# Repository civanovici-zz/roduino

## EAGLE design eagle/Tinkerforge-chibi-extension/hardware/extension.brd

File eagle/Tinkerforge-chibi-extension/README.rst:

Chibi Extension
===============

This repository contains the hardware design files. 
The software is included in the Master Brick software
and can be found at https://github.com/Tinkerforge/master-brick

Repository Content
------------------

hardware/:
 * Contains kicad project files and additionally schemetics as pdf

datasheets/:
 * Contains datasheets for sensors and complex ICs that are used

Hardware
--------

The hardware is designed with the open source EDA Suite KiCad
(http://kicad.sourceforge.net). Before you are able to open the files,
you have to install the Tinkerforge kicad-libraries
(https://github.com/Tinkerforge/kicad-libraries). You can either clone
them directly in hardware/ or clone them in a seperate folder and
symlink them into hardware/
(ln -s kicad_path/kicad-libraries project_path/hardware). After that you 
can open the .pro file in hardware/ with kicad and from there view and 
modify the schematics and the pcb layout.

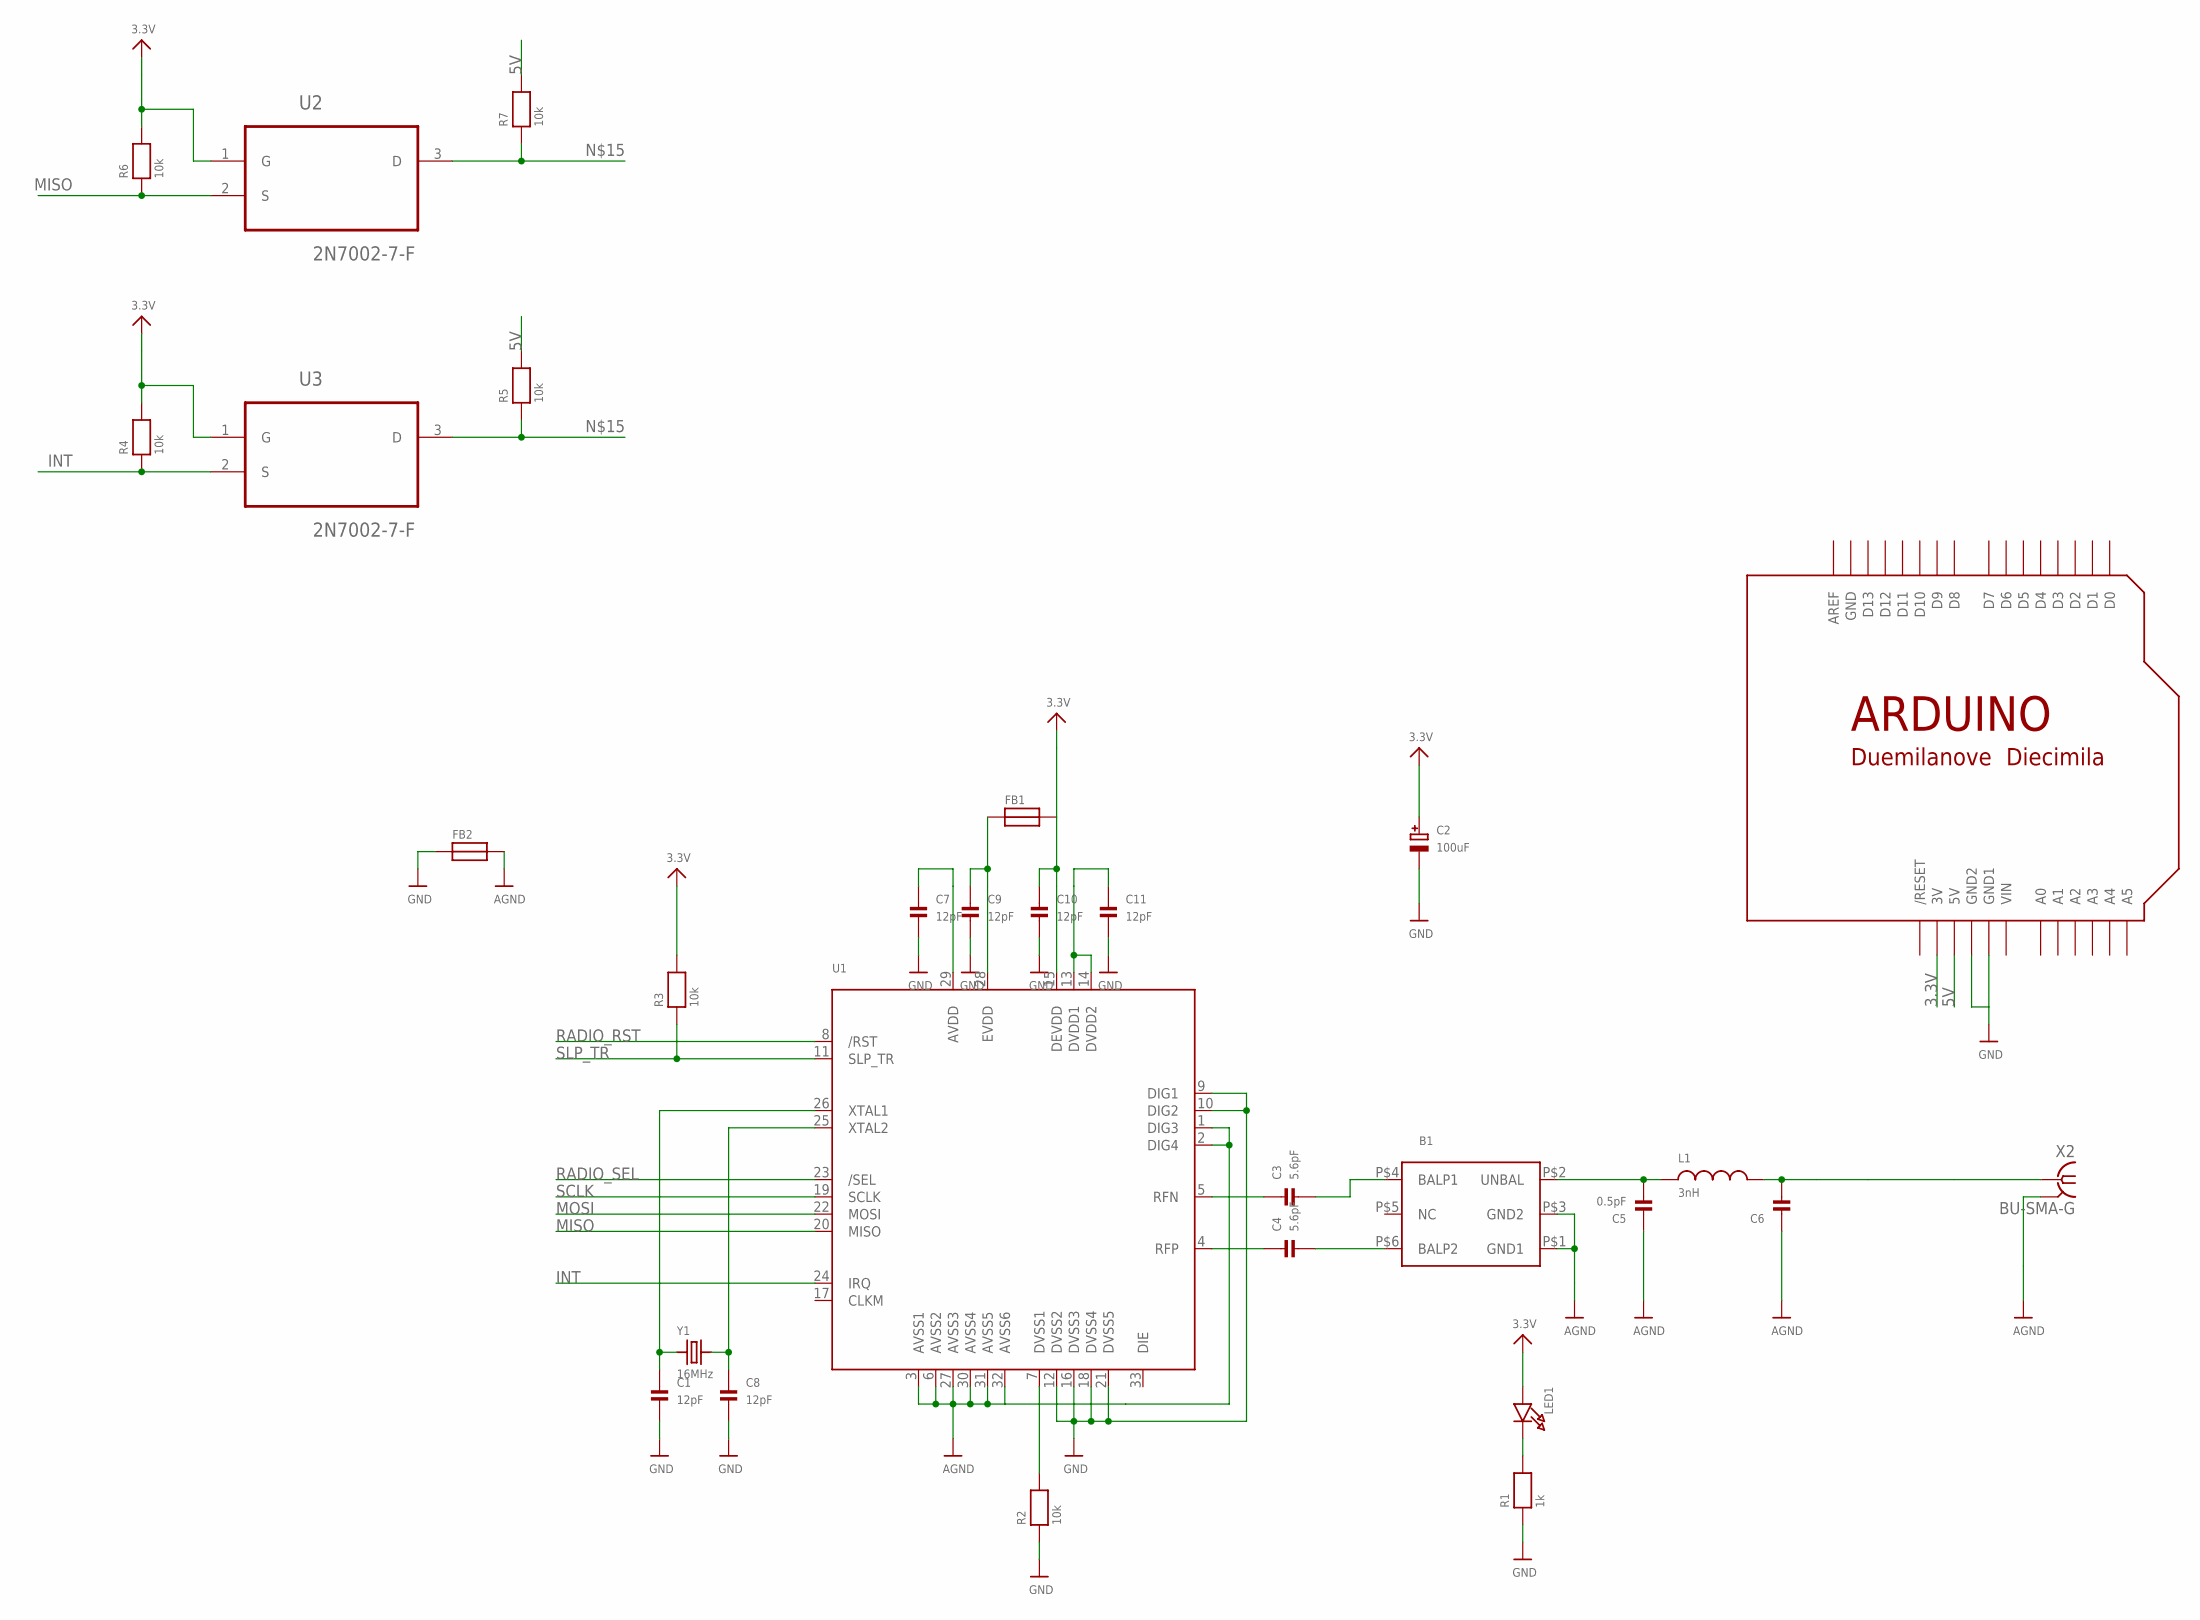
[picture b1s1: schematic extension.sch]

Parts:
B1: BALUN; BALUN1206
C1, C7, C8, C9, C10, C11: 12pF; 0805
C2: 100uF; PANASONIC_C
C3, C4: 5.6pF; 0805
C5: 0.5pF; 0805
C6: CAP_CERAMIC0805; 0805
FB1, FB2: FERRITE; 0603
L1: 3nH; 0805
LED1: LED0805; CHIPLED_0805
R1: 1k; 0805
R2, R3, R4, R5, R6, R7: 10k; 0805
U1: AT86RF212; 32QN2
U2, U3: 2N7002-7-F; SOT103P240X110-3N
U$1: ARDUINODUEMILANOVE; ARDUINO
X2: BU-SMA-G
Y1: 16MHz; HC49UP

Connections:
3.3V: C2.+, C10.1, FB1.2, LED1.A, R3.2, R4.2, R6.2, U1.15 (DEVDD), U2.1 (G), U3.1 (G), U$1.3V
5V: R5.2, R7.2, U$1.5V
AGND: B1.P$1 (GND1), B1.P$3 (GND2), C5.1, C6.1, FB2.2, U1.1 (DIG3), U1.2 (DIG4), U1.3 (AVSS1), U1.6 (AVSS2), U1.27 (AVSS3), U1.30 (AVSS4), U1.31 (AVSS5), U1.32 (AVSS6)
AGND1: X2.2 (GND)
GND: C1.2, C2.-, C7.2, C8.2, C9.2, C10.2, C11.2, FB2.1, R1.1, R2.1, U1.9 (DIG1), U1.10 (DIG2), U1.12 (DVSS2), U1.16 (DVSS3), U1.18 (DVSS4), U1.21 (DVSS5), U$1.GND, U$1.GND1, U$1.GND2, X2.3 (GND), X2.4 (GND), X2.5 (GND)
INT: R4.1, U1.24 (IRQ), U3.2 (S)
MISO: R6.1, U1.20 (MISO), U2.2 (S)
MOSI: U1.22 (MOSI)
unnamed: C3.1, U1.5 (RFN)
unnamed: C4.1, U1.4 (RFP)
unnamed: B1.P$4 (BALP1), C3.2
unnamed: B1.P$6 (BALP2), C4.2
unnamed: B1.P$2 (UNBAL), C5.2, L1.1
unnamed: C11.1, U1.13 (DVDD1), U1.14 (DVDD2)
unnamed: LED1.C, R1.2
unnamed: C6.2, L1.2, X2.1
unnamed: C1.1, U1.26 (XTAL1), Y1.1
unnamed: C8.1, U1.25 (XTAL2), Y1.2
unnamed: R2.2, U1.7 (DVSS1)
unnamed: C9.1, FB1.1, U1.28 (EVDD)
unnamed: C7.1, U1.29 (AVDD)
unnamed: R5.1, R7.1, U2.3 (D), U3.3 (D)
RADIO_RST: U1.8 (/RST)
RADIO_SEL: U1.23 (/SEL)
SCLK: U1.19 (SCLK)
SLP_TR: R3.1, U1.11 (SLP_TR)
VIN: U$1.VIN

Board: 2 copper layers, 29 parts (0 on the bottom side), 21 nets, no tracks yet.

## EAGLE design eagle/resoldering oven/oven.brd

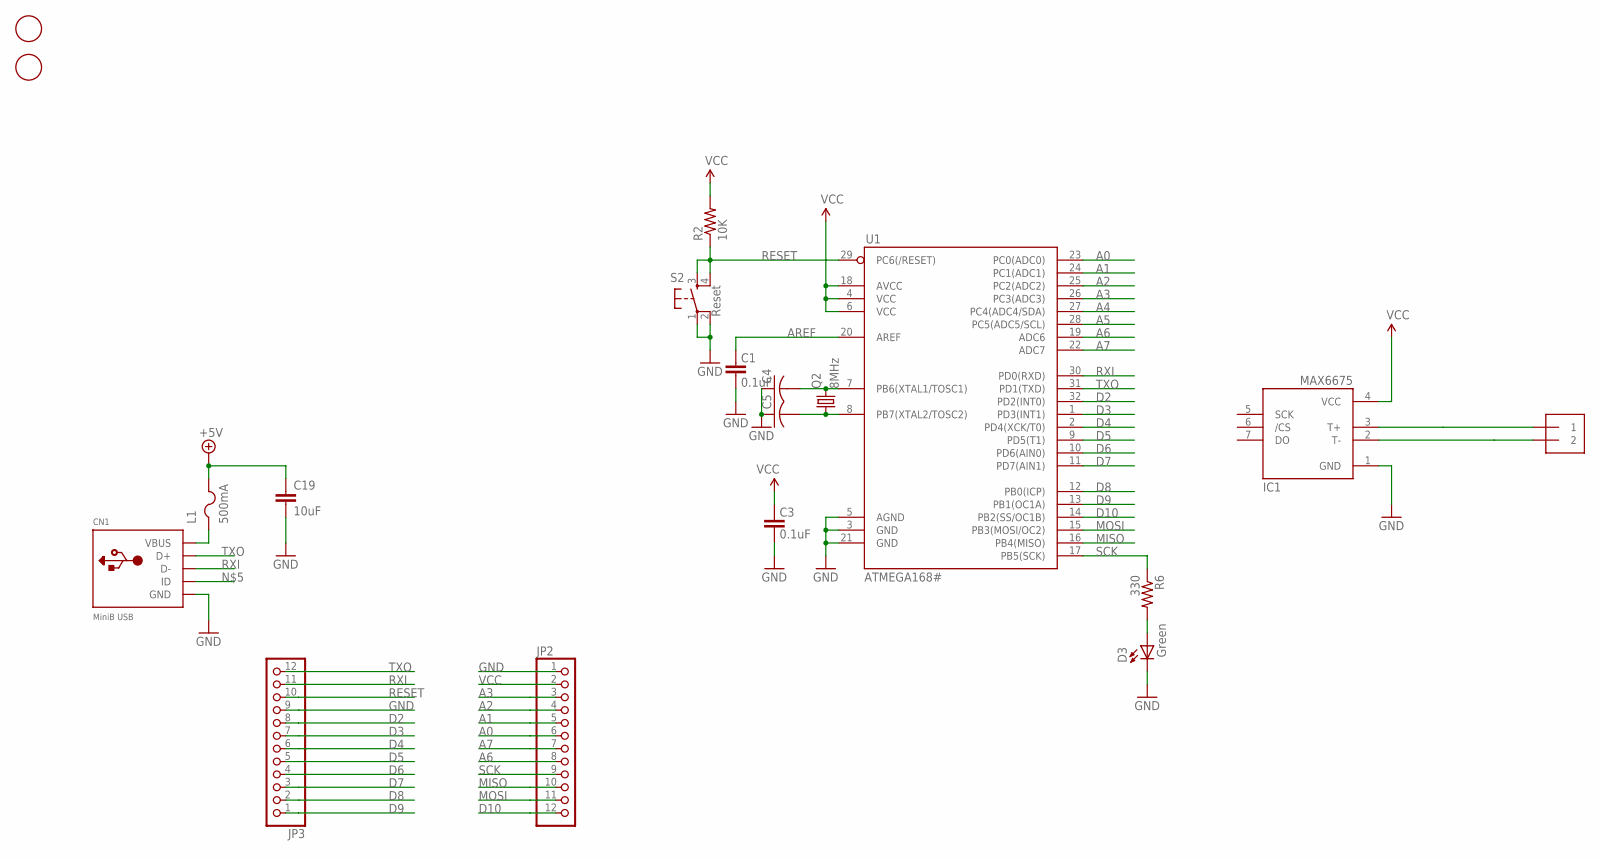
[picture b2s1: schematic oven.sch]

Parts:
C1, C3: 0.1uF; 0805
C4, C5: C-USC0805; C0805
C19: 10uF; C1206
CN1: MiniB USB; USB-MINIB
D3: Green; LED-0603
IC1: MAX6675; SO08
J1: 1X2-3.5MM; 3.5MMTERM
JP2, JP3: PINHD-1X12; 1X12
L1: 500mA; R1206
Q2: 8MHz; CTS406
R2: 10K; 0805
R6: 330; 0805
S2: Reset; TACTILE_SWITCH_SMD
U1: ATMEGA168#; TQFP32-08
U$5, U$6: FIDUCIAL; FIDUCIAL_1MM

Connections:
3.3V: IC1.4 (VCC)
A0: JP2.6, U1.23 (PC0(ADC0))
A1: JP2.5, U1.24 (PC1(ADC1))
A2: JP2.4, U1.25 (PC2(ADC2))
A3: JP2.3, U1.26 (PC3(ADC3))
A4: U1.27 (PC4(ADC4/SDA))
A5: U1.28 (PC5(ADC5/SCL))
A6: JP2.8, U1.19 (ADC6)
A7: JP2.7, U1.22 (ADC7)
AREF: C1.2, U1.20 (AREF)
D2: JP3.8, U1.32 (PD2(INT0))
D3: JP3.7, U1.1 (PD3(INT1))
D4: JP3.6, U1.2 (PD4(XCK/T0))
D5: JP3.5, U1.9 (PD5(T1))
D6: JP3.4, U1.10 (PD6(AIN0))
D7: JP3.3, U1.11 (PD7(AIN1))
D8: JP3.2, U1.12 (PB0(ICP))
D9: JP3.1, U1.13 (PB1(OC1A))
D10: JP2.12, U1.14 (PB2(SS/OC1B))
GND: C1.1, C3.1, C4.1, C5.1, C19.2, CN1.GND, D3.C, IC1.1 (GND), JP2.1, JP3.9, S2.1, S2.2, U1.3 (GND), U1.5 (AGND), U1.21 (GND)
GND1: IC1.2 (T-), J1.2
MISO: JP2.10, U1.16 (PB4(MISO))
MOSI: JP2.11, U1.15 (PB3(MOSI/OC2))
unnamed: C5.2, Q2.1, U1.8 (PB7(XTAL2/TOSC2))
unnamed: IC1.3 (T+), J1.1
unnamed: C4.2, Q2.3 (2), U1.7 (PB6(XTAL1/TOSC1))
unnamed: D3.A, R6.2
RESET: JP3.10, R2.1, S2.3, S2.4, U1.29 (PC6(/RESET))
RXI: CN1.D-, JP3.11, U1.30 (PD0(RXD))
SCK: JP2.9, R6.1, U1.17 (PB5(SCK))
TXO: CN1.D+, JP3.12, U1.31 (PD1(TXD))
VBUS: CN1.VBUS, L1.1
VCC: C3.2, C19.1, JP2.2, L1.2, R2.2, U1.4 (VCC), U1.6 (VCC), U1.18 (AVCC)

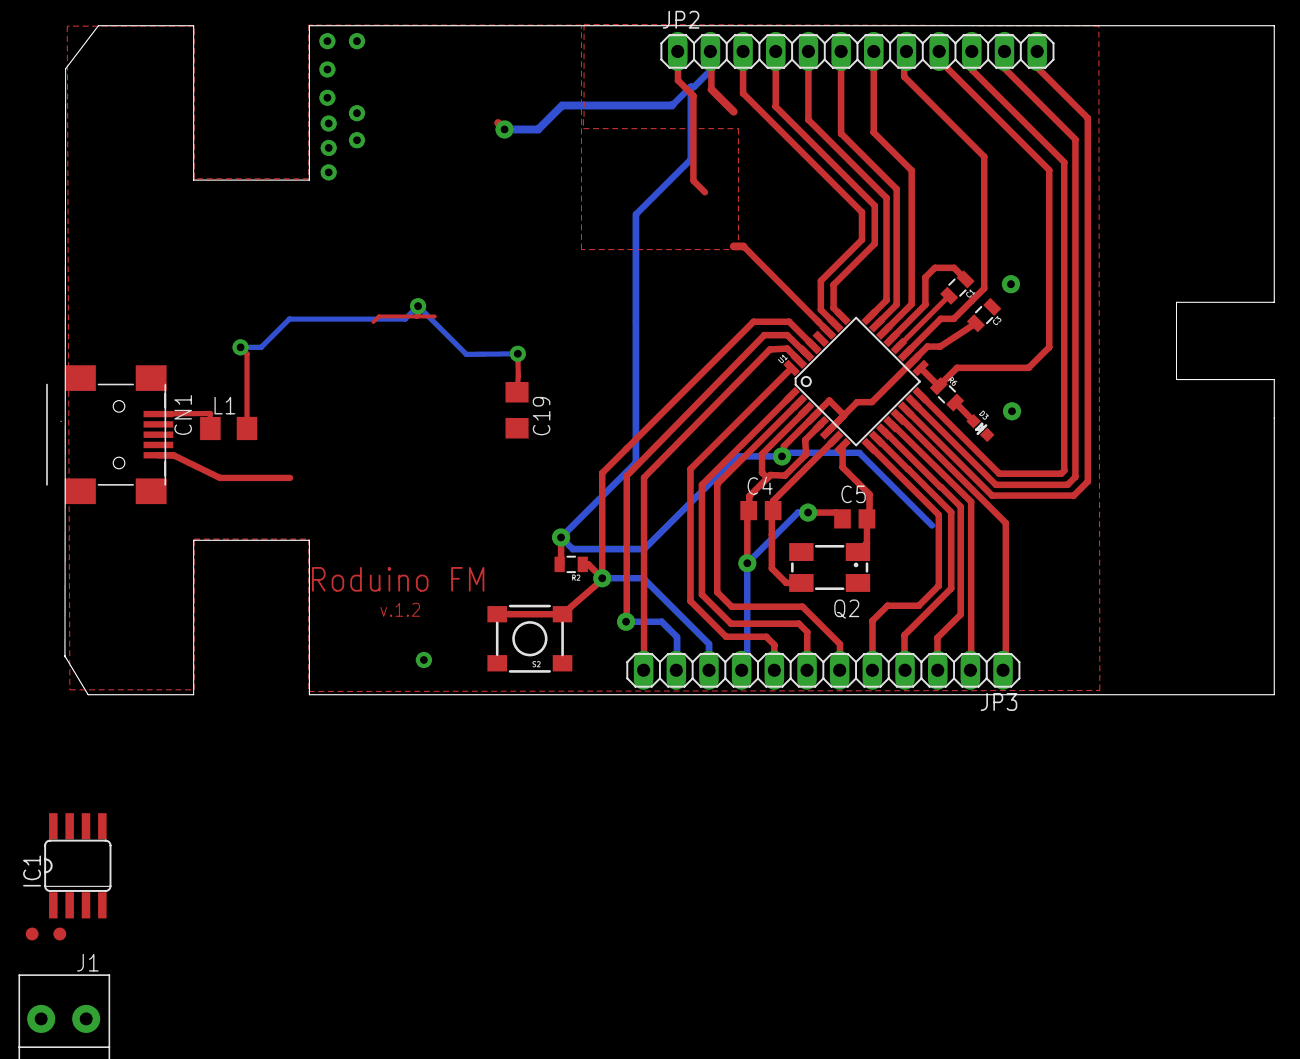
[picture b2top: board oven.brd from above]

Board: 2 copper layers, 94.0 x 52.0 mm, 19 parts (0 on the bottom side), 30 nets.

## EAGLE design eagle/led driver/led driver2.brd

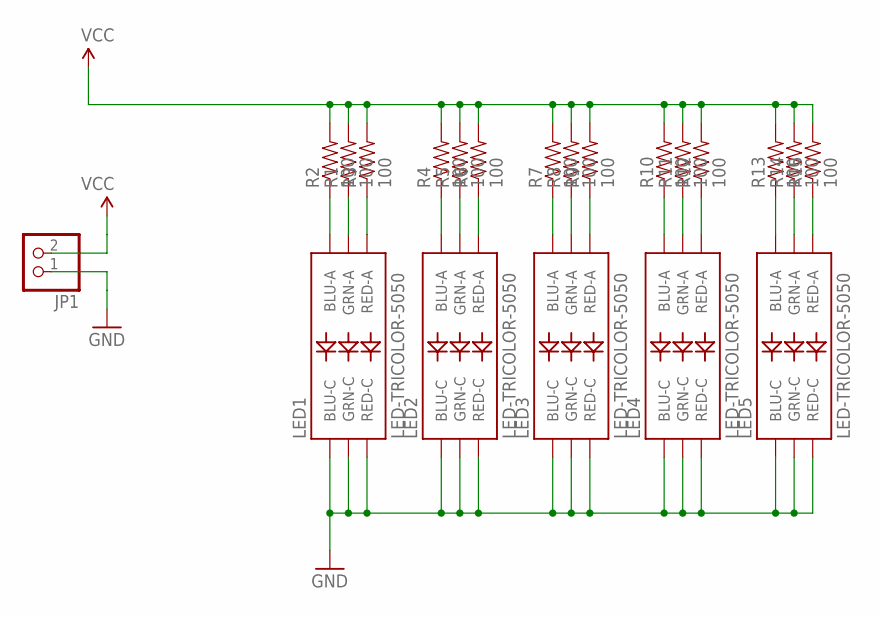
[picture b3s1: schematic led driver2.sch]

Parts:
JP1: PINHD-1X2; 1X02
LED1, LED2, LED3, LED4, LED5: LED-TRICOLOR-5050
R1, R2, R3, R4, R5, R6, R7, R8, R9, R10, R11, R12, R13, R14, R15: 100; 0603-RES

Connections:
GND: JP1.1, LED1.4 (BLU-C), LED1.5 (RED-C), LED1.6 (GRN-C), LED2.4 (BLU-C), LED2.5 (RED-C), LED2.6 (GRN-C), LED3.4 (BLU-C), LED3.5 (RED-C), LED3.6 (GRN-C), LED4.4 (BLU-C), LED4.5 (RED-C), LED4.6 (GRN-C), LED5.4 (BLU-C), LED5.5 (RED-C), LED5.6 (GRN-C)
unnamed: LED2.3 (BLU-A), R4.1
unnamed: LED2.1 (GRN-A), R5.1
unnamed: LED2.2 (RED-A), R6.1
unnamed: LED3.3 (BLU-A), R7.1
unnamed: LED3.1 (GRN-A), R8.1
unnamed: LED3.2 (RED-A), R9.1
unnamed: LED4.3 (BLU-A), R10.1
unnamed: LED4.1 (GRN-A), R11.1
unnamed: LED4.2 (RED-A), R12.1
unnamed: LED5.3 (BLU-A), R13.1
unnamed: LED5.1 (GRN-A), R14.1
unnamed: LED5.2 (RED-A), R15.1
unnamed: LED1.3 (BLU-A), R2.1
unnamed: LED1.1 (GRN-A), R1.1
unnamed: LED1.2 (RED-A), R3.1
VCC: JP1.2, R1.2, R2.2, R3.2, R4.2, R5.2, R6.2, R7.2, R8.2, R9.2, R10.2, R11.2, R12.2, R13.2, R14.2, R15.2

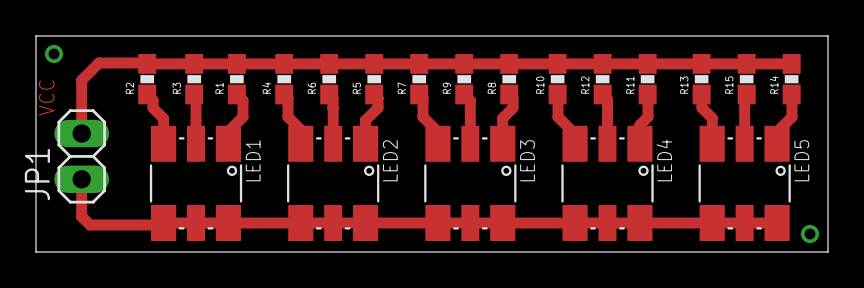
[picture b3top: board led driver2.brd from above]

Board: 2 copper layers, 44.0 x 12.0 mm, 21 parts (0 on the bottom side), 17 nets.

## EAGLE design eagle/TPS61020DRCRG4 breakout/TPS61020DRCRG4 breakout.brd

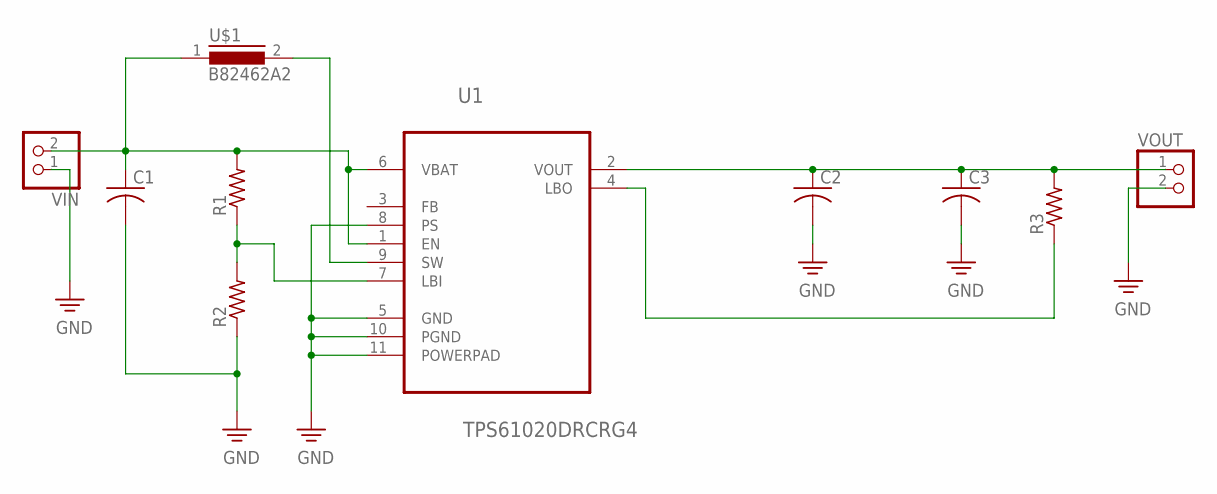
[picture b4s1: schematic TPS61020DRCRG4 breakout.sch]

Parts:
C1, C2: C-USC0805; C0805
C3: C-USC1206; C1206
R1, R2, R3: R-US_R0805; R0805
U1: TPS61020DRCRG4; SON50P300X300X100-11N
U$1: B82462A2; B8246A2682
VIN: PINHD-1X2; 1X02
VOUT: PINHD-1X2; 1X02

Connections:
unnamed: C2.1, C3.1, R3.2, U1.2 (VOUT), VOUT.1
unnamed: R1.1, R2.2, U1.7 (LBI)
unnamed: R3.1, U1.4 (LBO)
unnamed: C1.1, R1.2, U1.1 (EN), U1.6 (VBAT), U$1.1, VIN.2
unnamed: U1.9 (SW), U$1.2
PE: C1.2, C2.2, C3.2, R2.1, U1.5 (GND), U1.8 (PS), U1.10 (PGND), U1.11 (POWERPAD), VIN.1, VOUT.2

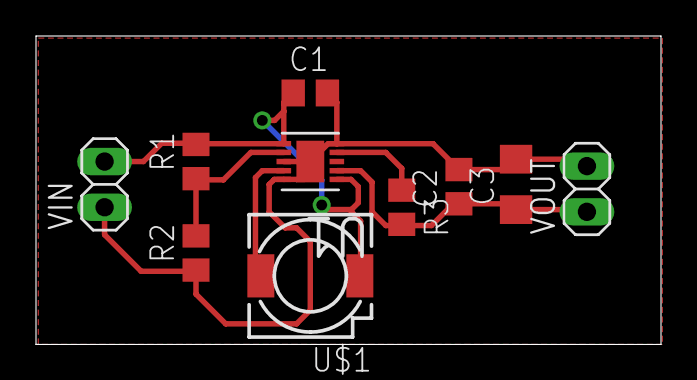
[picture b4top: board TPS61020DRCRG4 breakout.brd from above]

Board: 2 copper layers, 34.7 x 17.1 mm, 10 parts (0 on the bottom side), 6 nets.

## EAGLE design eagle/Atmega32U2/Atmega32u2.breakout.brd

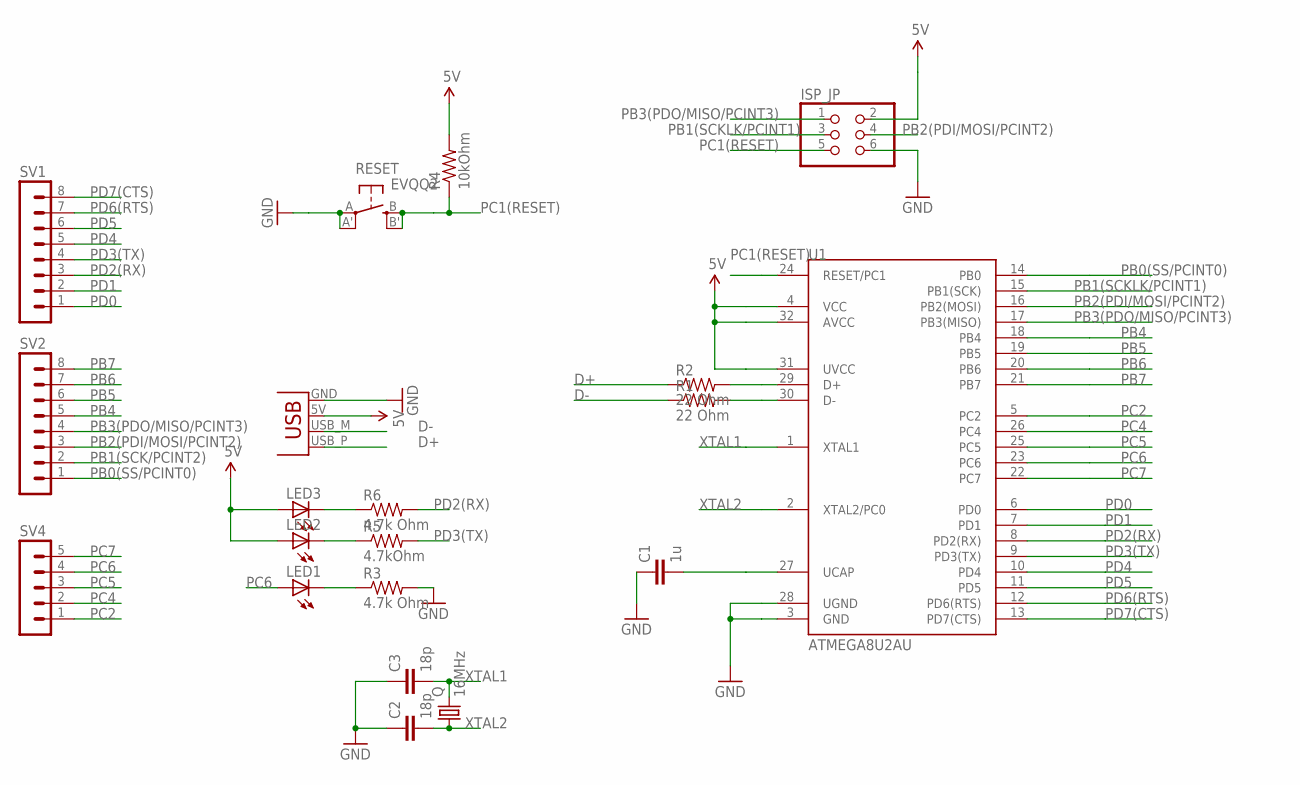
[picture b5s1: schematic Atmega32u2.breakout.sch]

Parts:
C1: 1u; 0805
C2, C3: 18p; 0805
ISP_JP: PINHD-2X3; 2X03
LED1, LED2, LED3: LED0603; LED-0603
Q: 16MHz; HC49US
R1, R2: 22 Ohm; 0805
R3, R6: 4.7k Ohm; 0805
R4: 10kOhm; 0805
R5: 4.7kOhm; 0805
RESET: EVQQ2; EVQ-Q2
SV1, SV2: MA08-1
SV4: MA05-1
U1: ATMEGA8U2AU; TQFP32-08
X1: USBPCB; USB-A-PCB

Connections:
5V: ISP_JP.2, LED2.A, LED3.A, R4.2, U1.4 (VCC), U1.31 (UVCC), U1.32 (AVCC), X1.5V (VBUS)
D+: R2.1, X1.USB_P (D+)
D-: R1.1, X1.USB_M (D-)
GND: C1.1, C2.1, C3.1, ISP_JP.6, R3.2, RESET.A, RESET.A' (P1), U1.3 (GND), U1.28 (UGND), X1.GND
unnamed: R2.2, U1.29 (D+)
unnamed: R1.2, U1.30 (D-)
unnamed: C1.2, U1.27 (UCAP)
unnamed: LED3.C, R6.1
unnamed: LED2.C, R5.1
unnamed: LED1.C, R3.1
PB0(SS/PCINT0): SV2.1, U1.14 (PB0)
PB1(SCK/PCINT2): SV2.2
PB1(SCKLK/PCINT1): ISP_JP.3, U1.15 (PB1(SCK))
PB2(PDI/MOSI/PCINT2): ISP_JP.4, SV2.3, U1.16 (PB2(MOSI))
PB3(PDO/MISO/PCINT3): ISP_JP.1, SV2.4, U1.17 (PB3(MISO))
PB4: SV2.5, U1.18 (PB4)
PB5: SV2.6, U1.19 (PB5)
PB6: SV2.7, U1.20 (PB6)
PB7: SV2.8, U1.21 (PB7)
PC1(RESET): ISP_JP.5, R4.1, RESET.B (S), RESET.B' (S1), U1.24 (RESET/PC1)
PC2: SV4.1, U1.5 (PC2)
PC4: SV4.2, U1.26 (PC4)
PC5: SV4.3, U1.25 (PC5)
PC6: LED1.A, SV4.4, U1.23 (PC6)
PC7: SV4.5, U1.22 (PC7)
PD0: SV1.1, U1.6 (PD0)
PD1: SV1.2, U1.7 (PD1)
PD2(RX): R6.2, SV1.3, U1.8 (PD2(RX))
PD3(TX): R5.2, SV1.4, U1.9 (PD3(TX))
PD4: SV1.5, U1.10 (PD4)
PD5: SV1.6, U1.11 (PD5)
PD6(RTS): SV1.7, U1.12 (PD6(RTS))
PD7(CTS): SV1.8, U1.13 (PD7(CTS))
XTAL1: C3.2, Q.2, U1.1 (XTAL1)
XTAL2: C2.2, Q.1, U1.2 (XTAL2/PC0)

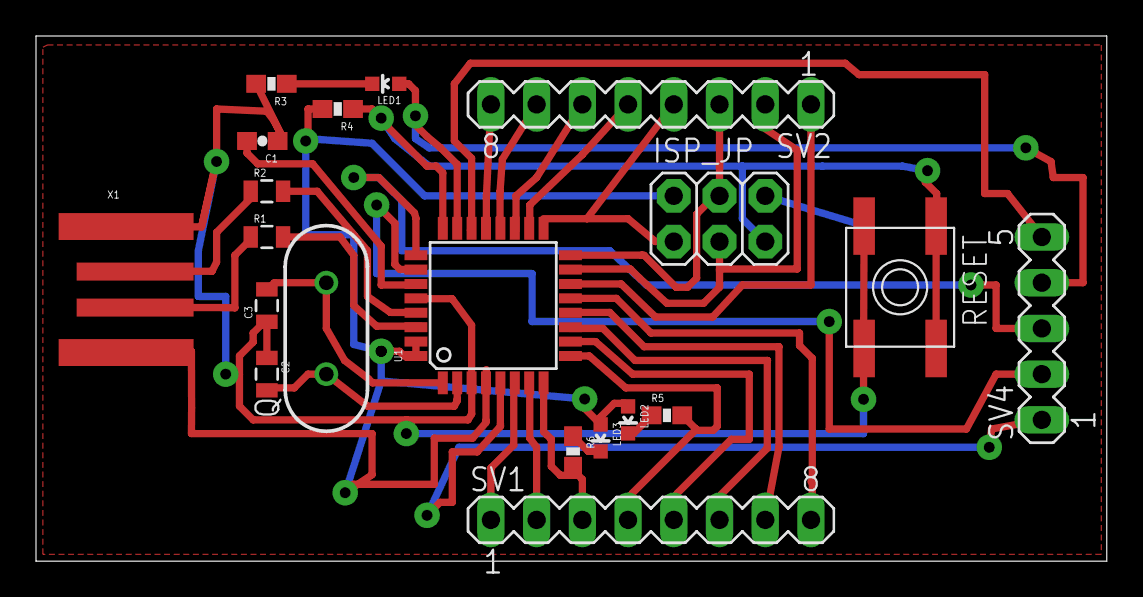
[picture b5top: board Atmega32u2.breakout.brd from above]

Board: 2 copper layers, 59.5 x 29.2 mm, 20 parts (0 on the bottom side), 34 nets.

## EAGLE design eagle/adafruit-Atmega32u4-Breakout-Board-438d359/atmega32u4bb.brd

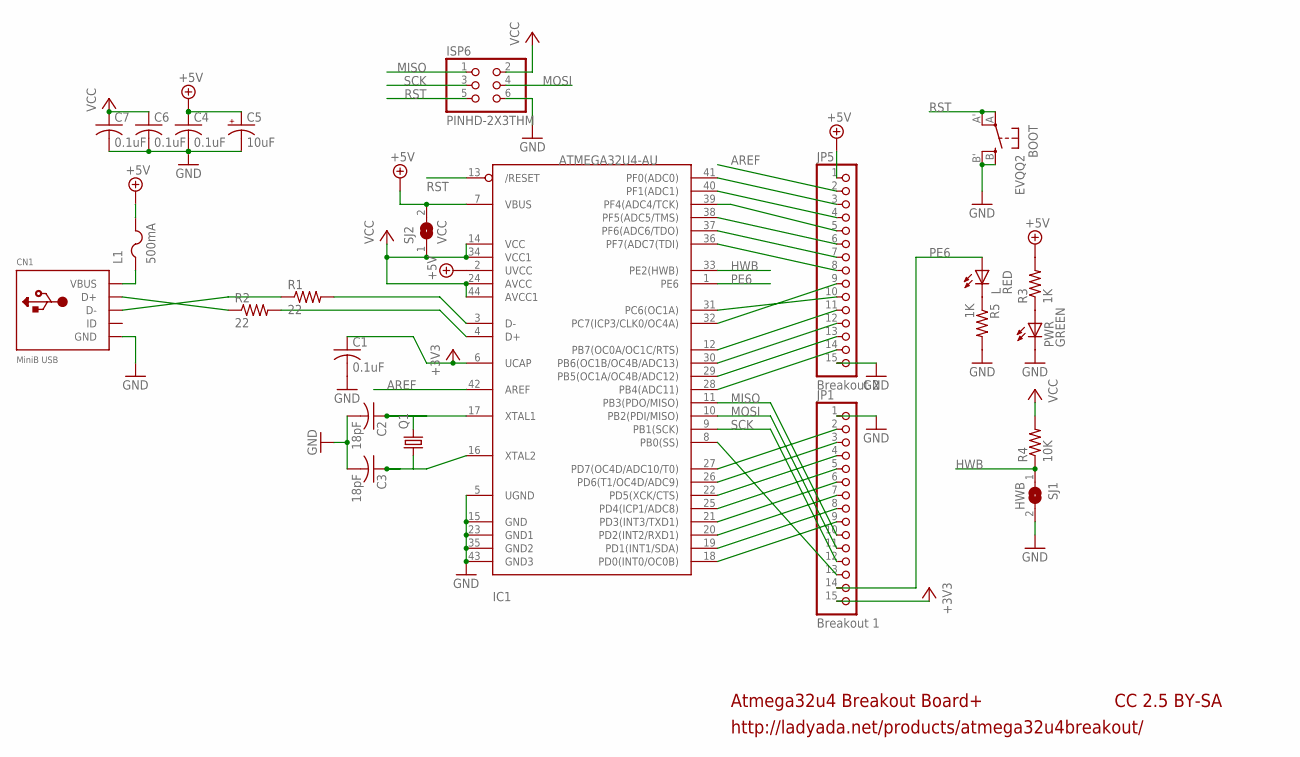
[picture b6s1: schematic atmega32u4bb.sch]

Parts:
BOOT: EVQQ2; EVQ-Q2
C1, C4, C6, C7: 0.1uF; C0805K
C2, C3: 18pF; C0805K
C5: 10uF; A/3216-18R
CN1: MiniB USB; USB-MINIB
IC1: ATMEGA32U4-AU; TQFP44
ISP6: PINHD-2X3THM; ISP6
JP1: Breakout 1; 1X15-CB
JP5: Breakout 2; 1X15-CB
L: RED; CHIPLED_0805
L1: 500mA; R1206
PWR: GREEN; CHIPLED_0805
Q1: CRYSTALHC49UP; HC49UP
R1, R2: 22; R0805
R3, R5: 1K; R0805
R4: 10K; R0805
SJ1: HWB; SJ
SJ2: VCC; SJ

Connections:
+3V3: C1.1, IC1.6 (UCAP), JP1.15
+5V: C4.1, C5.+, IC1.2 (UVCC), IC1.7 (VBUS), JP5.1, L1.2, R3.2, SJ2.2
AREF: IC1.42 (AREF), JP5.2
GND: BOOT.B (S), BOOT.B' (S1), C1.2, C2.2, C3.2, C4.2, C5.-, C6.2, C7.2, CN1.GND, IC1.5 (UGND), IC1.15 (GND), IC1.23 (GND1), IC1.35 (GND2), IC1.43 (GND3), ISP6.6, JP1.1, JP5.15, PWR.C, R5.2, SJ1.2
HWB: IC1.33 (PE2(HWB)), R4.1, SJ1.1
MISO: IC1.11 (PB3(PDO/MISO)), ISP6.1, JP1.10
MOSI: IC1.10 (PB2(PDI/MISO)), ISP6.4, JP1.11
unnamed: PWR.A, R3.1
unnamed: CN1.D+, R2.1
unnamed: IC1.3 (D-), R1.2
unnamed: IC1.4 (D+), R2.2
unnamed: CN1.D-, R1.1
unnamed: C2.1, IC1.17 (XTAL1), Q1.2
unnamed: C3.1, IC1.16 (XTAL2), Q1.1
unnamed: L.C, R5.1
PB0: IC1.8 (PB0(SS)), JP1.13
PB4: IC1.28 (PB4(ADC11)), JP5.14
PB5: IC1.29 (PB5(OC1A/OC4B/ADC12)), JP5.13
PB6: IC1.30 (PB6(OC1B/OC4B/ADC13)), JP5.12
PB7: IC1.12 (PB7(OC0A/OC1C/RTS)), JP5.11
PC6: IC1.31 (PC6(OC1A)), JP5.10
PC7: IC1.32 (PC7(ICP3/CLK0/OC4A)), JP5.9
PD0: IC1.18 (PD0(INT0/OC0B)), JP1.9
PD1: IC1.19 (PD1(INT1/SDA)), JP1.8
PD2: IC1.20 (PD2(INT2/RXD1)), JP1.7
PD3: IC1.21 (PD3(INT3/TXD1)), JP1.6
PD4: IC1.25 (PD4(ICP1/ADC8)), JP1.5
PD5: IC1.22 (PD5(XCK/CTS)), JP1.4
PD6: IC1.26 (PD6(T1/OC4D/ADC9)), JP1.3
PD7: IC1.27 (PD7(OC4D/ADC10/T0)), JP1.2
PE6: IC1.1 (PE6), JP1.14, L.A
PF0: IC1.41 (PF0(ADC0)), JP5.3
PF1: IC1.40 (PF1(ADC1)), JP5.4
PF4: IC1.39 (PF4(ADC4/TCK)), JP5.5
PF5: IC1.38 (PF5(ADC5/TMS)), JP5.6
PF6: IC1.37 (PF6(ADC6/TDO)), JP5.7
PF7: IC1.36 (PF7(ADC7(TDI)), JP5.8
RST: BOOT.A, BOOT.A' (P1), IC1.13 (/RESET), ISP6.5
SCK: IC1.9 (PB1(SCK)), ISP6.3, JP1.12
VBUS: CN1.VBUS, L1.1
VCC: C6.1, C7.1, IC1.14 (VCC), IC1.24 (AVCC), IC1.34 (VCC1), IC1.44 (AVCC1), ISP6.2, R4.2, SJ2.1

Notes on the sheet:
Atmega32u4 Breakout Board+
http://ladyada.net/products/atmega32u4breakout/
CC 2.5 BY-SA

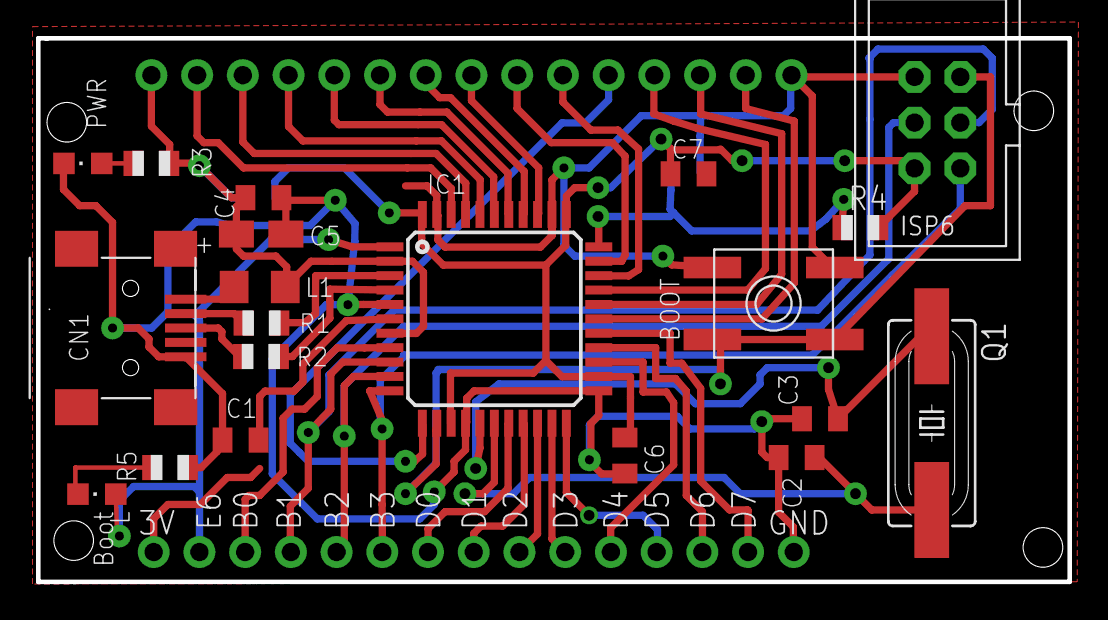
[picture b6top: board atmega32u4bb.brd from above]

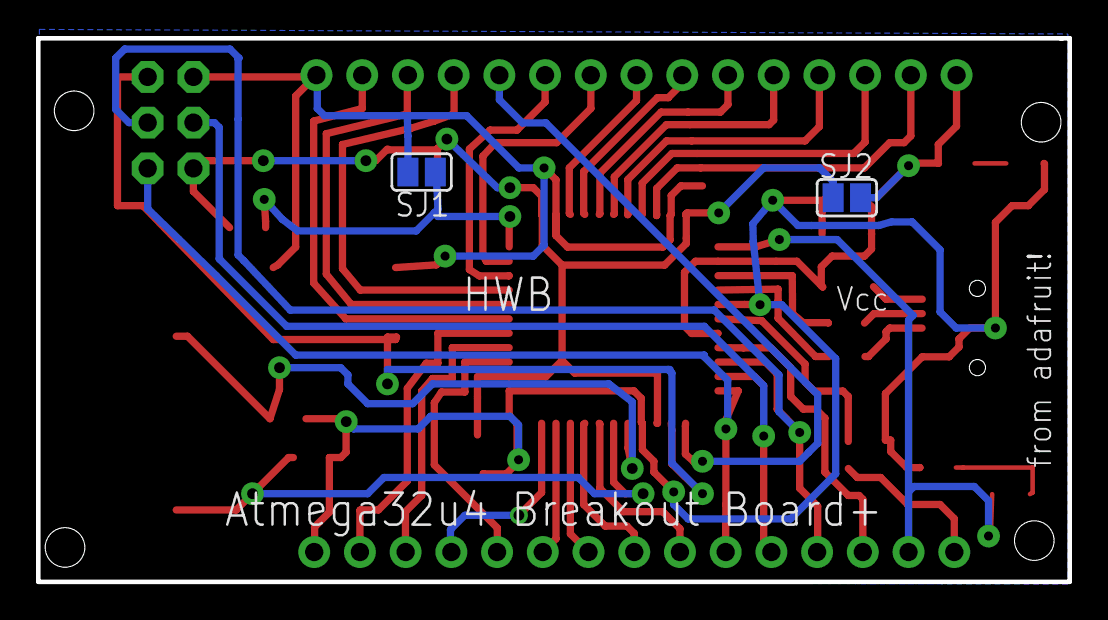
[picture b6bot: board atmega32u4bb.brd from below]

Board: 2 copper layers, 57.3 x 30.2 mm, 24 parts (2 on the bottom side), 41 nets.

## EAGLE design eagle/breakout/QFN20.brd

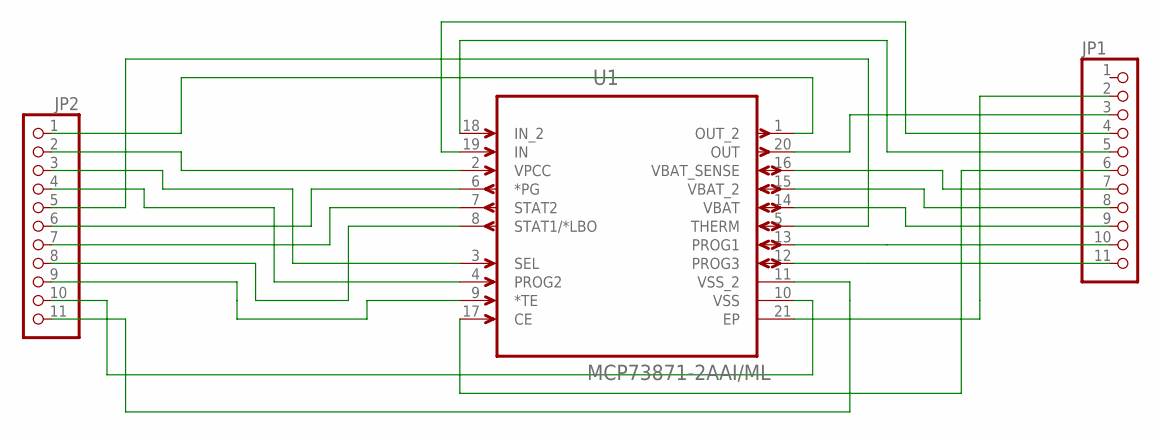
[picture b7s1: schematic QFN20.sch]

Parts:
JP1, JP2: PINHD-1X11; 1X11
U1: MCP73871-2AAI/ML; QFN50P400X400X100-21N

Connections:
unnamed: JP2.1, U1.1 (OUT_2)
unnamed: JP2.2, U1.2 (VPCC)
unnamed: JP2.3, U1.3 (SEL)
unnamed: JP2.4, U1.4 (PROG2)
unnamed: JP2.5, U1.5 (THERM)
unnamed: JP2.6, U1.6 (*PG)
unnamed: JP2.7, U1.7 (STAT2)
unnamed: JP2.8, U1.8 (STAT1/*LBO)
unnamed: JP2.9, U1.9 (*TE)
unnamed: JP2.10, U1.10 (VSS)
unnamed: JP2.11, U1.11 (VSS_2)
unnamed: JP1.11, U1.12 (PROG3)
unnamed: JP1.10, U1.13 (PROG1)
unnamed: JP1.9, U1.14 (VBAT)
unnamed: JP1.8, U1.15 (VBAT_2)
unnamed: JP1.7, U1.16 (VBAT_SENSE)
unnamed: JP1.6, U1.17 (CE)
unnamed: JP1.5, U1.18 (IN_2)
unnamed: JP1.4, U1.19 (IN)
unnamed: JP1.3, U1.20 (OUT)
unnamed: JP1.2, U1.21 (EP)

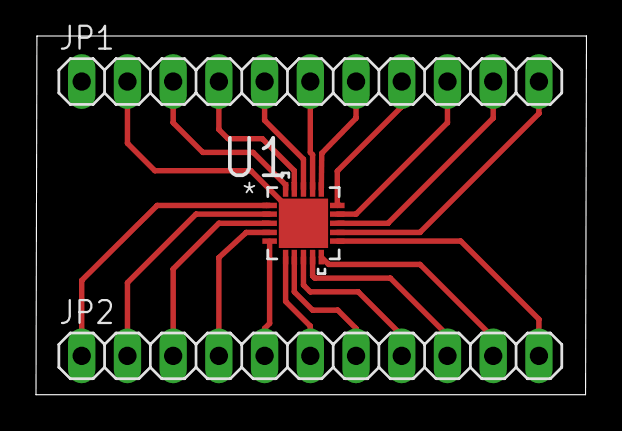
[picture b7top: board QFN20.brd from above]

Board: 2 copper layers, 30.6 x 19.9 mm, 3 parts (0 on the bottom side), 21 nets.
